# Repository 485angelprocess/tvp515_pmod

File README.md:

# TVP515 PMOD

PCB design for a TVP515. Takes PAL/NTSC composite video and outputs RGB parallel data. Designed with a pmod interface for FPGA video processing prototyping.

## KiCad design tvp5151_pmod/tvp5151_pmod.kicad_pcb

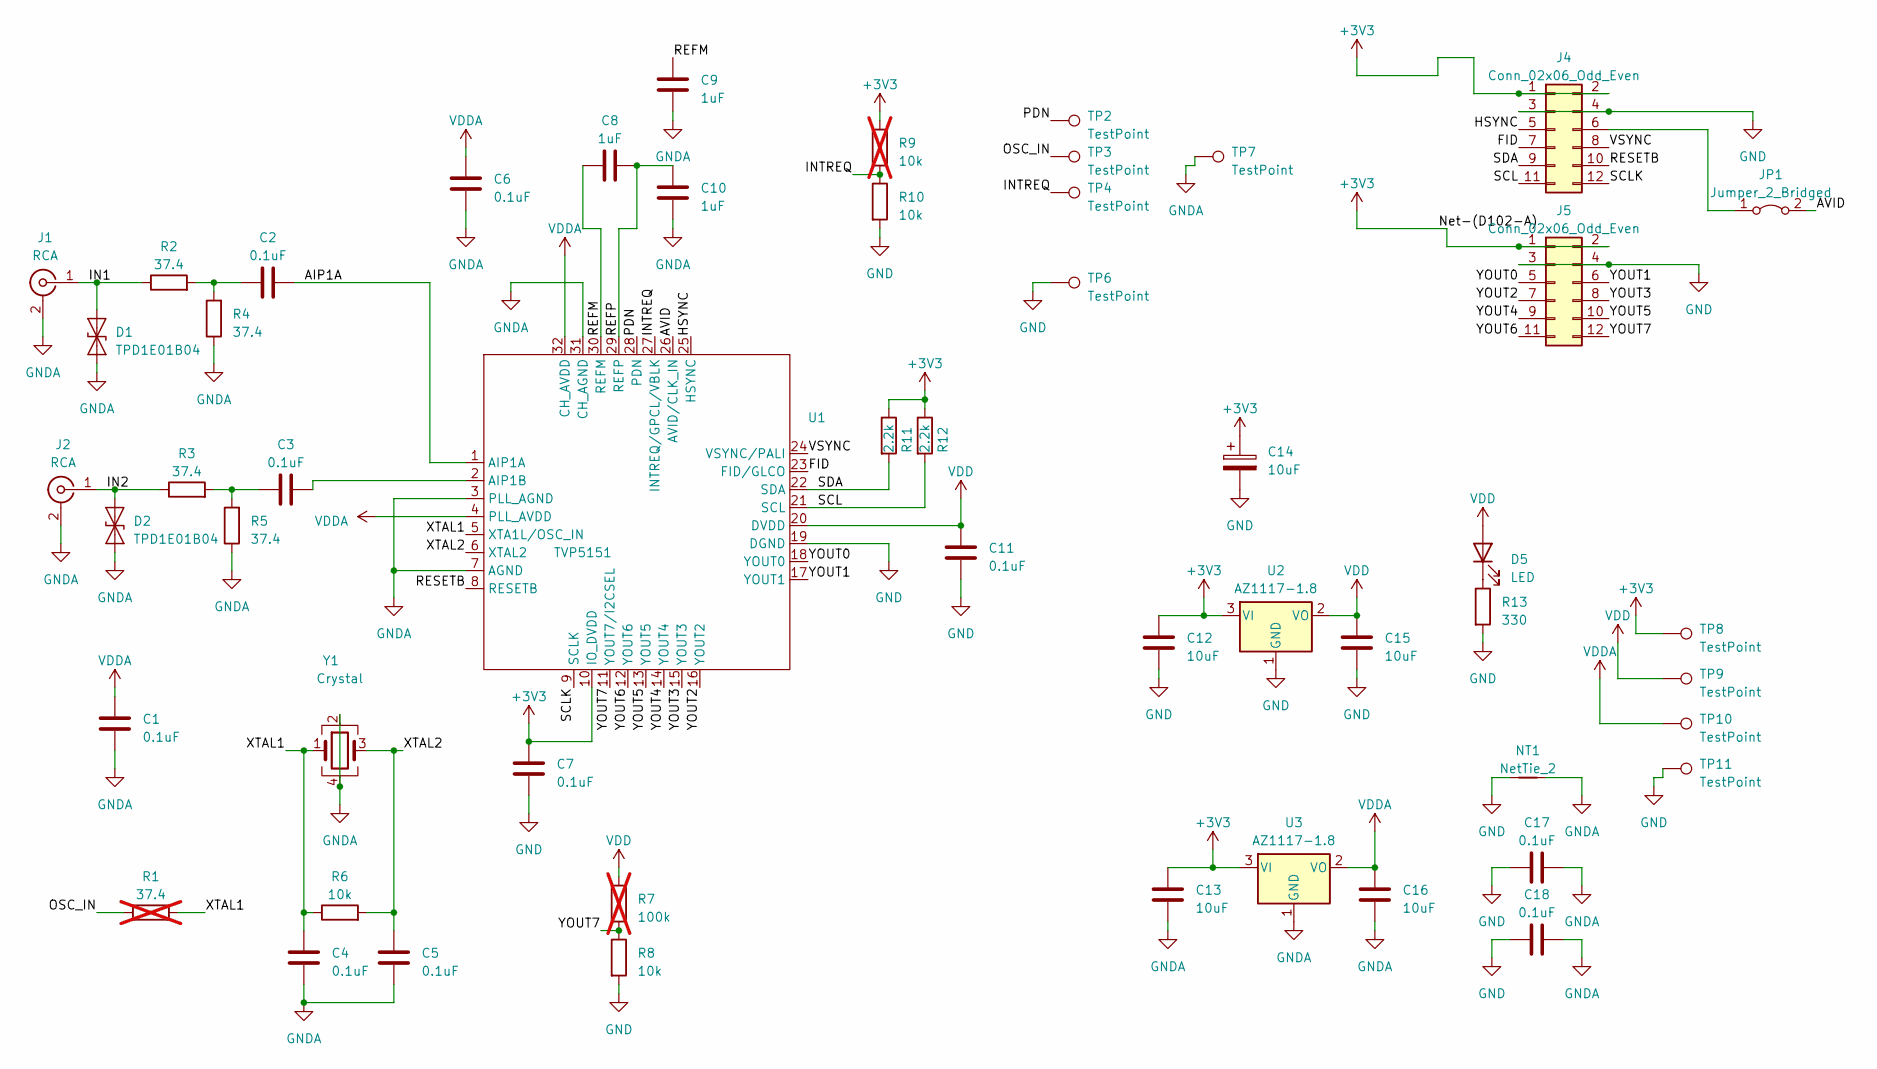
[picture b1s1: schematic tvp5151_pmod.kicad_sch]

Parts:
C1, C2, C3, C4, C5, C6, C7, C11, C17, C18: 0.1uF; C_0603_1608Metric
C8, C9, C10: 1uF; C_0603_1608Metric
C12, C13, C15, C16: 10uF; C_0805_2012Metric
C14: 10uF; CP_Radial_D5.0mm_P2.00mm
D1, D2: TPD1E01B04; D_0402_1005Metric_Pad0.77x0.64mm_HandSolder
D5: LED; LED_0603_1608Metric_Pad1.05x0.95mm_HandSolder
J1, J2: RCA
J4, J5: Conn_02x06_Odd_Even; PinHeader_2x06_P2.54mm_Horizontal
JP1: Jumper_2_Bridged; SolderJumper-2_P1.3mm_Bridged2Bar_Pad1.0x1.5mm
NT1: NetTie_2; NetTie-2_SMD_Pad2.0mm
R1: 37.4; R_0603_1608Metric_Pad0.98x0.95mm_HandSolder; not fitted
R2, R3, R4, R5: 37.4; R_0603_1608Metric_Pad0.98x0.95mm_HandSolder
R6, R8, R10: 10k; R_0603_1608Metric_Pad0.98x0.95mm_HandSolder
R7: 100k; R_0603_1608Metric_Pad0.98x0.95mm_HandSolder; not fitted
R9: 10k; R_0603_1608Metric_Pad0.98x0.95mm_HandSolder; not fitted
R11, R12: 2.2k; R_0603_1608Metric_Pad0.98x0.95mm_HandSolder
R13: 330; R_0603_1608Metric_Pad0.98x0.95mm_HandSolder
TP2, TP3, TP4, TP6, TP7, TP8, TP9, TP10, TP11: TestPoint; TestPoint_THTPad_1.5x1.5mm_Drill0.7mm
U1: TVP5151; TQFP-32_7x7mm_P0.8mm
U2, U3: AZ1117-1.8; SOT-223-3_TabPin2
Y1: Crystal; Crystal_SMD_Abracon_ABM8AIG-4Pin_3.2x2.5mm

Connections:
+3V3: C7.1, C12.1, C13.1, C14.1, J4.1, J4.2, J5.1, J5.2, R9.1, R11.1, R12.1, TP8.1, U1.10 (IO_DVDD), U2.3 (VI), U3.3 (VI)
/AIP1A: C2.2, U1.1 (AIP1A)
/AVID: JP1.2 (B), U1.26 (AVID/CLK_IN)
/FID: J4.7, U1.23 (FID/GLCO)
/HSYNC: J4.5, U1.25 (HSYNC)
/IN1: D1.2 (A2), J1.1 (In), R2.1
/IN2: D2.2 (A2), J2.1 (In), R3.1
/INTREQ: R9.2, R10.1, TP4.1, U1.27 (INTREQ/GPCL/VBLK)
/OSC_IN: R1.1, TP3.1
/PDN: TP2.1, U1.28 (PDN)
/REFM: C8.1, C9.1, U1.30 (REFM)
/REFP: C8.2, C10.1, U1.29 (REFP)
/RESETB: J4.10, U1.8 (RESETB)
/SCL: J4.11, R12.2, U1.21 (SCL)
/SCLK: J4.12, U1.9 (SCLK)
/SDA: J4.9, R11.2, U1.22 (SDA)
/VSYNC: J4.8, U1.24 (VSYNC/PALI)
/XTAL1: C4.2, R1.2, R6.1, U1.5 (XTA1L/OSC_IN), Y1.1
/XTAL2: C5.2, R6.2, U1.6 (XTAL2), Y1.3
/YOUT0: J5.5, U1.18 (YOUT0)
/YOUT1: J5.6, U1.17 (YOUT1)
/YOUT2: J5.7, U1.16 (YOUT2)
/YOUT3: J5.8, U1.15 (YOUT3)
/YOUT4: J5.9, U1.14 (YOUT4)
/YOUT5: J5.10, U1.13 (YOUT5)
/YOUT6: J5.11, U1.12 (YOUT6)
/YOUT7: J5.12, R7.2, R8.1, U1.11 (YOUT7/I2CSEL)
GND: C7.2, C11.2, C12.2, C14.2, C15.2, C17.1, C18.1, J4.3, J4.4, J5.3, J5.4, NT1.1, R8.2, R10.2, R13.2, TP6.1, TP11.1, U1.19 (DGND), U2.1 (GND)
GNDA: C1.1, C4.1, C5.1, C6.1, C9.2, C10.2, C13.2, C16.2, C17.2, C18.2, D1.1 (A1), D2.1 (A1), J1.2 (Ext), J2.2 (Ext), NT1.2, R4.1, R5.1, TP7.1, U1.3 (PLL_AGND), U1.7 (AGND), U1.31 (CH_AGND), U3.1 (GND), Y1.2, Y1.4
unnamed: C2.1, R2.2, R4.2
unnamed: C3.1, R3.2, R5.2
unnamed: D5.1 (K), R13.1
unnamed: J4.6, JP1.1 (A)
unnamed: C3.2, U1.2 (AIP1B)
VDD: C11.1, C15.1, D5.2 (A), R7.1, TP9.1, U1.20 (DVDD), U2.2 (VO)
VDDA: C1.2, C6.2, C16.1, TP10.1, U1.4 (PLL_AVDD), U1.32 (CH_AVDD), U3.2 (VO)

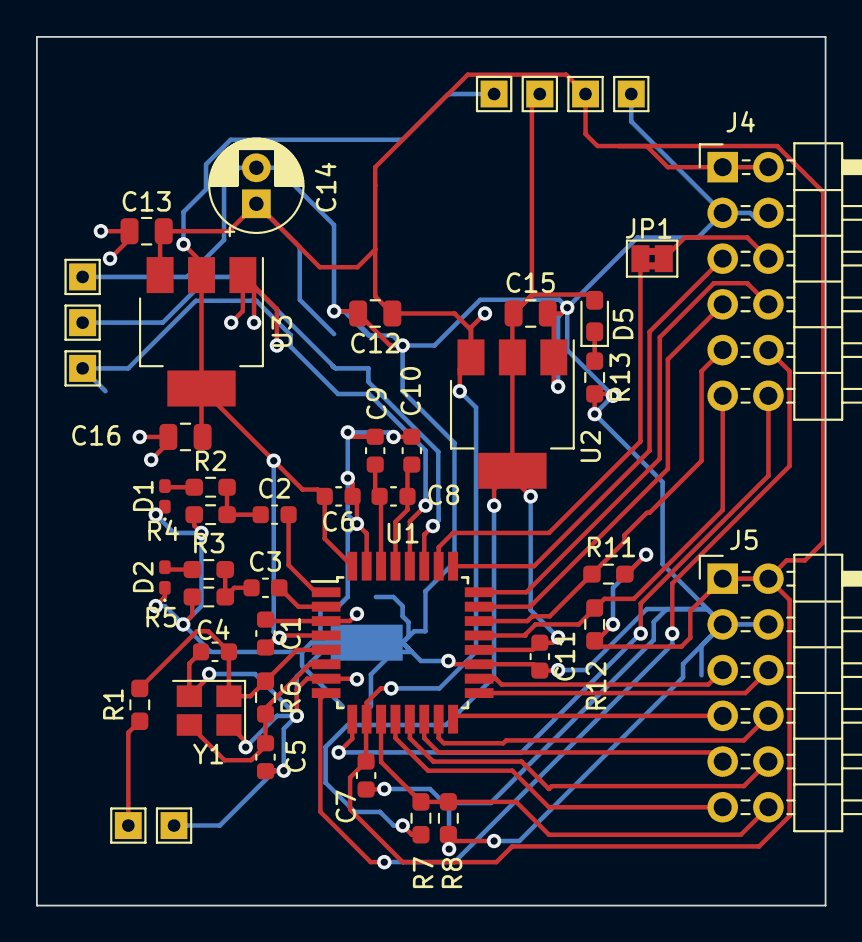
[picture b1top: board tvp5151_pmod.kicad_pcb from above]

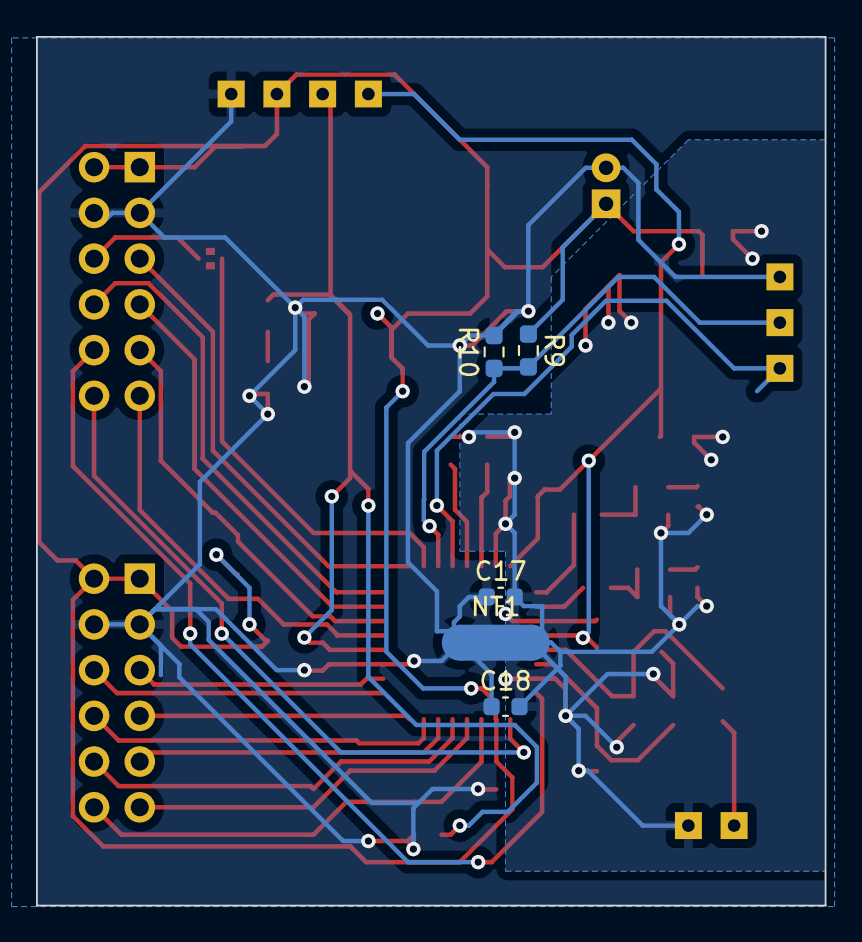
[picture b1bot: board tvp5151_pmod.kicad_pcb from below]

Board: 2 copper layers, 43.8 x 48.3 mm, 51 parts (5 on the bottom side), 36 nets.

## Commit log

2024-08-13 Added kicad files
